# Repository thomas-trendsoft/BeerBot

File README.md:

# BeerBot

Erster Versuch eines simplen mobilen und teilautonomen Roboter. Basis-Aufgabe wird
"Hol ein Bier" oder anderen Gegenstandes von der Lager-Position bis zum anfordernden Benutzer.

Basis Aufgaben für die erste Version:

- Navigation / Mapping (Basis Orientierung)
- Object Detection (Bier erkennung)
- Steuerung der Aktuatoren zum Heben (Bier aufnehmen)

## Basis Aufbauplan

### Software

- TinySLAM als Navigation und Mapping Algorithmus
- YOLOvX as Object Detection Network mit eigenem Training für die Bierdose
- KiCAD für Schaltpläne
- FreeCAD für Bauteile und 3D Druck-Teile

### Hardware

Für die elektronische Steuerung und Wahrnehmung sind bisher folgende Sensoren und Bauteile vorgesehen:

- Raspberry Pi 3 (oder 4) als Basisboard
- HC-SR04 Distanzsensor für eine Feature und Hinderniserkennung
- 28BYJ-48 Schrittmotoren als Host für die Distanzmessung in unterschiedlichen Richtungen
- ULN2003 Schrittmotor Steuerung zum Ansprechen der Schrittmotoren
- MPU 6050 Gyroscope für die Berechnung von Winkeländerung und Beschleunigung
- 2 DC Motoren für den 2 Rad Antrieb  
- L298N Motortreiber für den Antrieb

Eine genaue Einkaufsliste soll später erstellt werden zum Nachbauen.

#### Hardware

##### PIN Belegung

Die PIN Nummer entspricht der GPIO Nummer bei der Raspberry Belegung.

- DC Motor 1
    - Pin0 = enable
    - Pin1 = in1
    - Pin7 = in2
- DC Motor 2
    - Pin9 = enable
    - Pin10 = in1
    - Pin11 = in2
- Servo Motor 1
    - Pin12 = PWM
- Servo Motor 2
    - Pin13 = PWM
- Schritt Motor
    - Pin22 = StepPin0
    - Pin23 = StepPin1
    - Pin24 = StepPin2
    - Pin25 = StepPin3
- HC-SR04 Distanzsensor
    - Pin17 = Echo
    - Pin18 = Trigger
- Taster1
    - Pin14 = IN
- Taster2
    - Pin15 = IN
- ODO Meter 1
    - Pin5 = IN
- ODO Meter 2
    - Pin6 = IN
- Gyroscope / MPU 6050
    - Pin2 = SDA (have to check I2C on Raspberry if not exact wrong)
    - Pin3 = SCL

##### Datenblätter/Papers

- TinySLAM: https://ieeexplore.ieee.org/document/5707402
- MPU6050 Basic Datasheet: https://invensense.tdk.com/wp-content/uploads/2015/02/MPU-6000-Datasheet1.pdf
- MPU6050 Register Datasheet: https://invensense.tdk.com/wp-content/uploads/2015/02/MPU-6000-Register-Map1.pdf

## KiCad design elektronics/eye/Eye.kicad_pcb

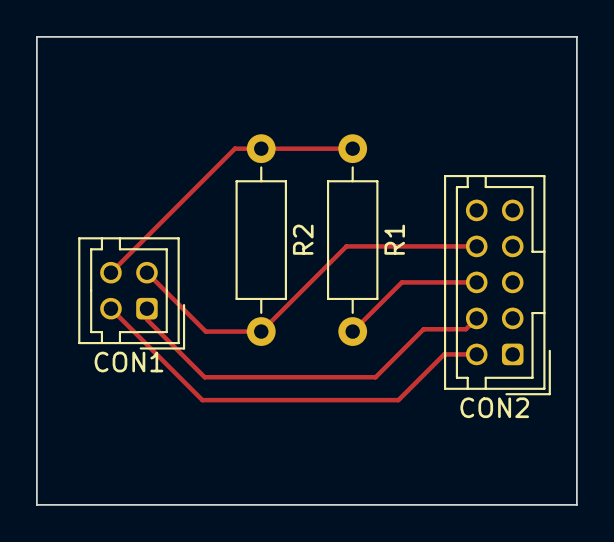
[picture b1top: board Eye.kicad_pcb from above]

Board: 2 copper layers, 30.0 x 26.0 mm, 4 parts (0 on the bottom side), 5 nets.

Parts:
CON1: PI; JAE_LY20-4P-DT1_2x02_P2.00mm_Vertical
CON2: HC-SR04; JAE_LY20-10P-DT1_2x05_P2.00mm_Vertical
R1: R330; R_Axial_DIN0207_L6.3mm_D2.5mm_P10.16mm_Horizontal
R2: R10K; R_Axial_DIN0207_L6.3mm_D2.5mm_P10.16mm_Horizontal

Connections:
unnamed: CON1.a1, CON2.b2
unnamed: CON1.a2, CON2.b4, R2.2
unnamed: CON1.b1, CON2.b1
unnamed: CON1.b2, R1.1, R2.1
unnamed: CON2.b3, R1.2

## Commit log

2020-11-23 initial files from first tries
2020-11-24 cpp project steps / simple python calibration
2020-11-24 first eyescanner steps dist measure
2020-11-24 base structured ported to c++
2020-11-24 drive motor implementation / driveAround test
2020-11-27 stepper tested / distance tested / eyescanner tested
2020-11-27 first cpp drive around
2020-11-27 param optimized / i2c dev param
2020-11-28 odo meter integration
2020-11-28 odo meter based driving first step
2020-11-29 init pos update handling
2020-12-02 estimate pos update (forward) / eye scan with multiple value return
2020-12-02 first slam steps
2020-12-03 small tinyslam steps
2020-12-05 tinyslam / client ui init
2020-12-05 server base module added
2020-12-05 odo pins / server module
2020-12-07 java ui (more simple) / client handler steps / small fixes
2020-12-07 client communication basics
2020-12-07 ui control steps
2020-12-16 fix client accept socket thread / send client handler msg / client ui refactoring
2020-12-17 some mem handling (c++ learn steps) / handshake / ui steps
2020-12-18 base network handling / ui pause button and first info pull test
2020-12-18 commands for move button
2020-12-19 add electronics and 3d part first steps
2020-12-19 first little remote control by client / new podest design / pcb with drill holes
2020-12-20 ui refactoring / clean up / backward fix
2020-12-26 protocol for position pull / very simple pid controller for forward driving
2020-12-27 more dynamic pid control
2020-12-28 client long run task / pid tuning / ui position units
2020-12-28 ui steps
2020-12-28 eye scan as array for tinyslam / client task thread isolation fix / start mapping function
2020-12-29 prepare mapping
2021-01-03 c++ / threads / map widget / logging
2021-01-03 add missing updates
2021-01-13 bluetooth base steps / guest list steps / object detection tests
